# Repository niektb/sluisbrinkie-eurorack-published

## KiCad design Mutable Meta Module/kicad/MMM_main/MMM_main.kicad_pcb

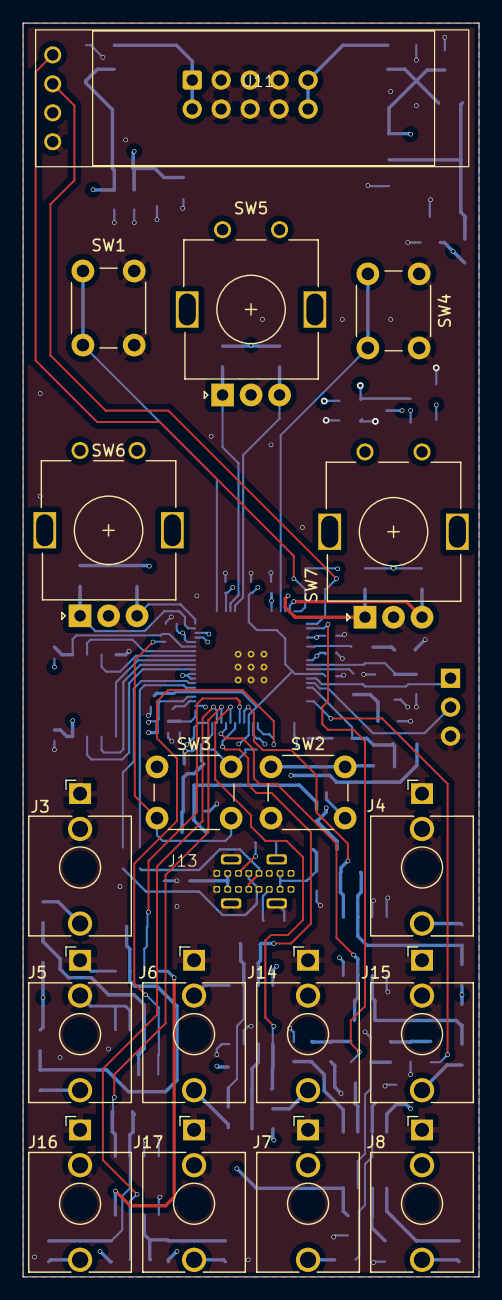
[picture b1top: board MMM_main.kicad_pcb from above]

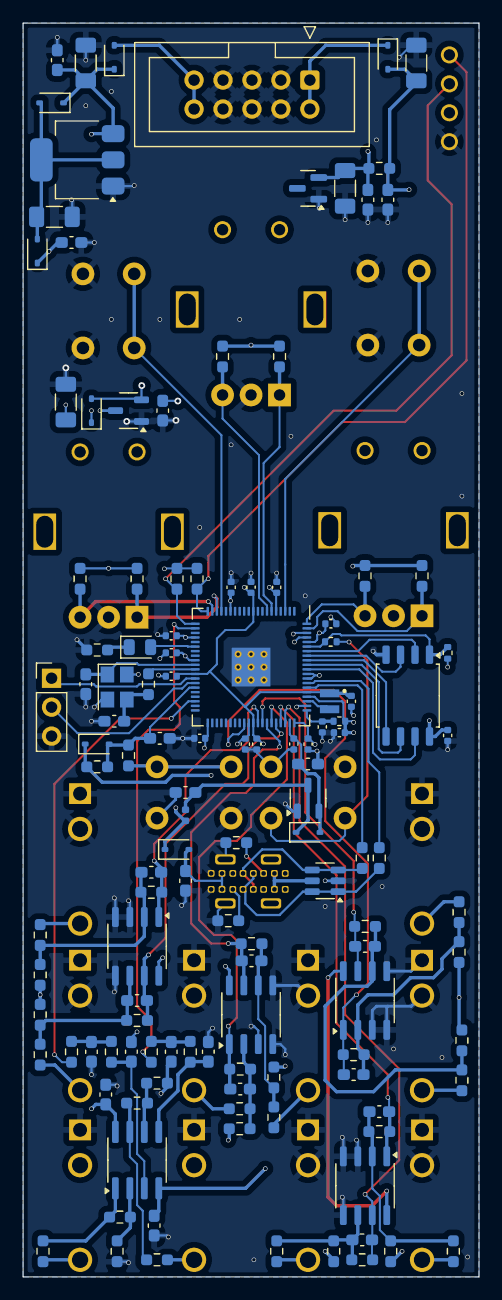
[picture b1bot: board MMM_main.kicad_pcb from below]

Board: 4 copper layers, 40.0 x 110.0 mm, 145 parts (126 on the bottom side), 83 nets.

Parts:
C1, C2, C3, C4, C12: 22uF; C_1206_3216Metric_Pad1.33x1.80mm_HandSolder
C5, C11, C13, C14, C17, C42, C43, C51: 100n; C_0603_1608Metric_Pad1.08x0.95mm_HandSolder
C7, C9, C10, C28: 4.7u; C_0402_1005Metric
C8, C15, C18, C19, C20, C21, C22, C23, C24, C25, C26, C27: 100n; C_0402_1005Metric
C16, C29, C44: 4u7F; C_0603_1608Metric_Pad1.08x0.95mm_HandSolder
C30, C34, C37, C38, C45, C46, C47, C48: 1n; C_0603_1608Metric_Pad1.08x0.95mm_HandSolder
C31, C35: 33p; C_0603_1608Metric_Pad1.08x0.95mm_HandSolder
C32, C41: 10n; C_0603_1608Metric_Pad1.08x0.95mm_HandSolder
C36, C40: 4n7; C_0603_1608Metric_Pad1.08x0.95mm_HandSolder
D6: C2290; LED_0805_2012Metric
D9, D10, D11, D12, D13, D14, D15, D16: 1N5819WS; D_SOD-323
FB1: BLM15H; L_0402_1005Metric
J1: Eurorack Power; IDC-Header_2x05_P2.54mm_Vertical
J2: Conn_01x03; PinHeader_1x03_P2.54mm_Vertical
J3: CV1; Jack_3.5mm_QingPu_WQP-PJ398SM_Vertical_CircularHoles_3D
J4: CV2; Jack_3.5mm_QingPu_WQP-PJ398SM_Vertical_CircularHoles_3D
J5: CV3; Jack_3.5mm_QingPu_WQP-PJ398SM_Vertical_CircularHoles_3D
J6: CV4; Jack_3.5mm_QingPu_WQP-PJ398SM_Vertical_CircularHoles_3D
J7: OUT1; Jack_3.5mm_QingPu_WQP-PJ398SM_Vertical_CircularHoles_3D
J8: OUT2; Jack_3.5mm_QingPu_WQP-PJ398SM_Vertical_CircularHoles_3D
J13: USB_C_Receptacle_USB2.0_16P; UJ20-C-V-C-2-SMT-TR
J14: CV5; Jack_3.5mm_QingPu_WQP-PJ398SM_Vertical_CircularHoles_3D
J15: CV6; Jack_3.5mm_QingPu_WQP-PJ398SM_Vertical_CircularHoles_3D
J16: CV7; Jack_3.5mm_QingPu_WQP-PJ398SM_Vertical_CircularHoles_3D
J17: CV8; Jack_3.5mm_QingPu_WQP-PJ398SM_Vertical_CircularHoles_3D
L1: AOTA-B201610S3R3-101-T; L_pol_2016
R1: 10k; R_0402_1005Metric
R2, R7, R11, R14, R21, R34, R41, R45, R47, R49: 200k; R_0603_1608Metric_Pad0.98x0.95mm_HandSolder
R3: 33; R_0402_1005Metric
R4, R8, R15, R20, R22, R36, R40, R46, R48, R50: 100k; R_0603_1608Metric_Pad0.98x0.95mm_HandSolder
R5, R12, R27, R28, R51, R52, R53, R54: 33k; R_0603_1608Metric_Pad0.98x0.95mm_HandSolder
R6: 1k; R_0402_1005Metric
R13: 2k; R_0603_1608Metric_Pad0.98x0.95mm_HandSolder
R16, R25, R26, R29, R30, R31, R32: 10k; R_0603_1608Metric_Pad0.98x0.95mm_HandSolder
R17: 330R; R_0603_1608Metric_Pad0.98x0.95mm_HandSolder
R18, R19: 27R; R_0603_1608Metric_Pad0.98x0.95mm_HandSolder
R23, R24, R33, R42: 1k; R_0603_1608Metric_Pad0.98x0.95mm_HandSolder
R35, R37, R38, R39: 3k9; R_0603_1608Metric_Pad0.98x0.95mm_HandSolder
R43, R44: 2k2; R_0603_1608Metric_Pad0.98x0.95mm_HandSolder
R55, R56: 5k1; R_0603_1608Metric_Pad0.98x0.95mm_HandSolder
SW1, SW2, SW3, SW4: SW_Push; SW_PUSH_6mm_H13mm
SW5, SW6, SW7: RotaryEncoder; RotaryEncoder_Alps_EC11E_Vertical_H20mm
U1: RP2350_80QFN; RP2350-QFN-80-1EP_10x10_P0.4mm_EP3.4x3.4mm_ThermalVias
U2: AMS1117-5.0; SOT-223-3_TabPin2
U4: W25Q128JVS; SOIC-8_5.3x5.3mm_P1.27mm
U5, U12: XC6206P332MR; SOT-23-3
U6, U9, U13, U14: MCP6002-I-SN; SO-8_3.9x4.9mm_P1.27mm
U7: LM4040DBZ-10; SOT-23
U8: TL072; SOIC-8_3.9x4.9mm_P1.27mm
U10: USBLC6-2SC6; SOT-23-6
U11: SSD1306; OLED_0.91inch
Y1: ABM8-272-T3; Crystal_SMD_3225-4Pin_3.2x2.5mm

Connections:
+1V1: C8.1, C9.1, C10.1, C18.1, L1.1, U1.10 (DVDD), U1.32 (DVDD), U1.51 (DVDD), U1.65 (VREG_FB)
+3V3: C7.1, C15.1, C19.1, C20.1, C21.1, C22.1, C23.1, C24.1, C25.1, C26.1, C29.1, D13.2 (A), D15.1 (K), R1.1, R3.1, R16.2, R25.2, R26.2, R29.2, R30.2, R31.2, R32.2, R43.2, R44.2, U1.5 (IOVDD), U1.15 (IOVDD), U1.24 (IOVDD), U1.29 (IOVDD), U1.41 (IOVDD), U1.50 (IOVDD), U1.60 (IOVDD), U1.64 (VREG_VIN), U1.68 (USB_OTP_VDD), U1.69 (QSPI_IOVDD), U1.76 (IOVDD), U4.8 (VCC), U5.2 (VO), U6.8 (V+), U9.8 (V+), U11.3 (VCC), U13.8 (V+), U14.8 (V+)
+3V3A: C27.1, C44.1, D16.2 (A), U1.59 (ADC_AVDD), U12.2 (VO)
+5V: C3.1, C17.1, D9.1 (K), D13.1 (K), D14.1 (K), FB1.1, U5.3 (VI)
+12V: C1.1, C5.1, C42.1, D10.1 (K), D12.1 (K), U2.3 (VI), U8.8 (V+)
-12V: C2.2, C11.1, C43.2, D11.2 (A), R13.1, U8.4 (V-)
/-10V_REF: C12.1, C13.1, R2.2, R7.2, R11.2, R13.2, R14.2, R21.2, R45.2, R47.2, R49.2, U7.2 (A)
/CC1: J13.A5 (CC1), R55.1
/CC2: J13.B5 (CC2), R56.1
/CV1: C30.2, R5.1, U1.49 (GPIO40_ADC0), U6.1
/CV1_JACK: J3.T, R4.2
/CV2: C34.2, R12.1, U1.52 (GPIO41_ADC1), U9.1
/CV2_JACK: J4.T, R8.2
/CV3: C37.2, R27.1, U1.53 (GPIO42_ADC2), U6.7
/CV3_JACK: J5.T, R15.2
/CV4: C38.2, R28.1, U1.54 (GPIO43_ADC3), U13.7
/CV4_JACK: J6.T, R22.2
/CV5: C45.2, R51.1, U1.55 (GPIO44_ADC4), U13.1
/CV5_JACK: J14.T, R20.2
/CV6: C46.2, R52.1, U1.56 (GPIO45_ADC5), U9.7
/CV6_JACK: J15.T, R46.2
/CV7: C47.2, R53.1, U1.57 (GPIO46_ADC6), U14.1
/CV7_JACK: J16.T, R48.2
/CV8: C48.2, R54.1, U1.58 (GPIO47_ADC7), U14.7
/CV8_JACK: J17.T, R50.2
/D+: J13.A6 (D+), J13.B6 (D+), R18.2, U10.1 (I/O1), U10.6 (I/O1)
/D-: J13.A7 (D-), J13.B7 (D-), R19.1, U10.3 (I/O2), U10.4 (I/O2)
/DM: R19.2, U1.66 (USB_DM)
/DP: R18.1, U1.67 (USB_DP)
/ENC1A: R25.1, SW5.A, U1.6 (GPIO8)
/ENC1B: R26.1, SW5.B, U1.7 (GPIO9)
/ENC2A: R30.1, SW6.A, U1.79 (GPIO2)
/ENC2B: R29.1, SW6.B, U1.80 (GPIO3)
/ENC3A: R32.1, SW7.A, U1.18 (GPIO18)
/ENC3B: R31.1, SW7.B, U1.19 (GPIO19)
/OUT1: R37.2, U1.22 (GPIO22)
/OUT2: R38.2, U1.38 (GPIO30)
/QSPI_SCLK: U1.71 (QSPI_SCLK), U4.6 (CLK)
/QSPI_SD0: U1.72 (QSPI_SD0), U4.5 (DI(IO0))
/QSPI_SD1: U1.74 (QSPI_SD1), U4.2 (DO(IO1))
/QSPI_SD2: U1.73 (QSPI_SD2), U4.3 (IO2)
/QSPI_SD3: U1.70 (QSPI_SD3), U4.7 (IO3)
/QSPI_SS: R1.2, R6.1, U1.75 (QSPI_SS), U4.1 (~CS)
/RESET: R17.1, SW2.2
/SCL: R43.1, U1.21 (GPIO21), U11.2 (SCL)
/SDA: R44.1, U1.20 (GPIO20), U11.1 (SDA)
/SW1: SW1.2, U1.3 (GPIO6)
/SW2: SW4.2, U1.17 (GPIO17)
/VBUS: C16.1, D9.2 (A), J13.A4 (VBUS), J13.A9 (VBUS), J13.B4 (VBUS), J13.B9 (VBUS), U10.5 (VBUS)
/VREG_LX: L1.2, U1.63 (VREG_LX)
/~USB_BOOT: R6.2, SW3.2
GND: C1.2, C2.1, C3.2, C4.2, C5.2, C7.2, C8.2, C9.2, C10.2, C11.2, C12.2, C13.2, C14.2, C15.2, C16.2, C17.2, C18.2, C19.2, C20.2, C21.2, C22.2, C23.2, C24.2, C25.2, C26.2, C27.2, C28.2, C29.2, C31.2, C32.2, C35.2, C36.2, C40.2, C41.2, C42.2, C43.1, C44.2, C51.2, J1.3, J1.4, J1.5, J1.6, J1.7, J1.8, J2.3, J3.S, J3.TN, J4.S, J4.TN, J5.S, J5.TN, J6.S, J6.TN, J7.S, J8.S, J13.A1 (GND), J13.A12 (GND), J13.B1 (GND), J13.B12 (GND), J13.SH1 (SHIELD), J13.SH2 (SHIELD), J13.SH3 (SHIELD), J13.SH4 (SHIELD), J14.S, J14.TN, J15.S, J15.TN, J16.S, J16.TN, J17.S, J17.TN, R24.1, R36.2, R40.2, R55.2, R56.2, SW1.1, SW2.1, SW3.1, SW4.1, SW5.C, SW6.C, SW7.C, U1.62 (VREG_PGND), U1.81 (GND), U2.1 (GND), U4.4 (GND), U5.1 (GND), U6.3 (+), U6.4 (V-), U6.5 (+), U7.1 (K), U9.3 (+), U9.4 (V-), U9.5 (+), U10.2 (GND), U11.4 (GND), U12.1 (GND), U13.3 (+), U13.4 (V-), U13.5 (+), U14.3 (+), U14.4 (V-), U14.5 (+), Y1.2, Y1.4
unnamed: C35.1, R23.2, Y1.3
unnamed: C36.1, R35.2, R37.1
unnamed: C40.1, R38.1, R39.2
unnamed: D6.2 (A), U1.26 (GPIO25)
unnamed: D6.1 (K), R24.2
unnamed: D10.2 (A), J1.9, J1.10
unnamed: D11.1 (K), J1.1, J1.2
unnamed: C4.1, D12.2 (A), D14.2 (A), U2.2 (VO)
unnamed: C14.1, D15.2 (A), R16.1, R17.2, U1.35 (RUN)
unnamed: C51.1, D16.1 (K), FB1.2, U12.3 (VI)
unnamed: J2.1, U1.33 (SWCLK)
unnamed: J2.2, U1.34 (SWD)
unnamed: J7.T, R33.1
unnamed: J8.T, R42.1
unnamed: R33.2, R34.1, U8.7
unnamed: R41.1, R42.2, U8.1
unnamed: C28.1, R3.2, U1.61 (VREG_AVDD)
unnamed: C31.1, U1.30 (XIN), Y1.1
unnamed: R23.1, U1.31 (XOUT)
unnamed: C30.1, R2.1, R4.1, R5.2, U6.2 (-)
unnamed: C37.1, R14.1, R15.1, R27.2, U6.6 (-)
unnamed: C41.1, R39.1, U8.3 (+)
unnamed: R40.1, R41.2, U8.2 (-)
unnamed: C32.1, R35.1, U8.5 (+)
unnamed: R34.2, R36.1, U8.6 (-)
unnamed: C34.1, R7.1, R8.1, R12.2, U9.2 (-)
unnamed: C46.1, R45.1, R46.1, R52.2, U9.6 (-)
unnamed: C45.1, R11.1, R20.1, R51.2, U13.2 (-)
unnamed: C38.1, R21.1, R22.1, R28.2, U13.6 (-)
unnamed: C47.1, R47.1, R48.1, R53.2, U14.2 (-)
unnamed: C48.1, R49.1, R50.1, R54.2, U14.6 (-)

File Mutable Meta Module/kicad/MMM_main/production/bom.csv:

Designator,Footprint,Quantity,Value,LCSC Part #
"C1, C12, C2, C3, C4",1206,5,22uF,
"C10, C28, C7, C9",0402,4,4.7u,
"C11, C13, C14, C17, C42, C43, C5, C51",0603,8,100n,
"C15, C18, C19, C20, C21, C22, C23, C24, C25, C26, C27, C8",0402,12,100n,
"C16, C29, C44",0603,3,4u7F,
"C30, C34, C37, C38, C45, C46, C47, C48",0603,8,1n,
"C31, C35",0603,2,33p,
"C32, C41",0603,2,10n,
"C36, C40",0603,2,4n7,
"D10, D11, D12, D13, D14, D15, D16, D9",D_SOD-323,8,1N5819WS,
D6,0805,1,C2290,
FB1,0402,1,BLM15H,
J1,IDC-Header_2x05_P2.54mm_Vertical,1,Eurorack Power,
J13,UJ20-C-V-C-2-SMT-TR,1,USB_C_Receptacle_USB2.0_16P,
J14,Jack_3.5mm_QingPu_WQP-PJ398SM_Vertical_CircularHoles_3D,1,CV5,
J15,Jack_3.5mm_QingPu_WQP-PJ398SM_Vertical_CircularHoles_3D,1,CV6,
J16,Jack_3.5mm_QingPu_WQP-PJ398SM_Vertical_CircularHoles_3D,1,CV7,
J17,Jack_3.5mm_QingPu_WQP-PJ398SM_Vertical_CircularHoles_3D,1,CV8,
J3,Jack_3.5mm_QingPu_WQP-PJ398SM_Vertical_CircularHoles_3D,1,CV1,
J4,Jack_3.5mm_QingPu_WQP-PJ398SM_Vertical_CircularHoles_3D,1,CV2,
J5,Jack_3.5mm_QingPu_WQP-PJ398SM_Vertical_CircularHoles_3D,1,CV3,
J6,Jack_3.5mm_QingPu_WQP-PJ398SM_Vertical_CircularHoles_3D,1,CV4,
J7,Jack_3.5mm_QingPu_WQP-PJ398SM_Vertical_CircularHoles_3D,1,OUT1,
J8,Jack_3.5mm_QingPu_WQP-PJ398SM_Vertical_CircularHoles_3D,1,OUT2,
L1,L_pol_2016,1,AOTA-B201610S3R3-101-T,
R1,0402,1,10k,
"R11, R14, R2, R21, R34, R41, R45, R47, R49, R7",0603,10,200k,
"R12, R27, R28, R5, R51, R52, R53, R54",0603,8,33k,
R13,0603,1,2k,
"R15, R20, R22, R36, R4, R40, R46, R48, R50, R8",0603,10,100k,
"R16, R25, R26, R29, R30, R31, R32",0603,7,10k,
R17,0603,1,330R,
"R18, R19",0603,2,27R,
"R23, R24, R33, R42",0603,4,1k,
R3,0402,1,33,
"R35, R37, R38, R39",0603,4,3k9,
"R43, R44",0603,2,2k2,
"R55, R56",0603,2,5k1,
R6,0402,1,1k,
"SW1, SW2, SW3, SW4",SW_PUSH_6mm_H13mm,4,SW_Push,
"SW5, SW6, SW7",RotaryEncoder_Alps_EC11E_Vertical_H20mm,3,RotaryEncoder,
U1,RP2350-QFN-80-1EP_10x10_P0.4mm_EP3.4x3.4mm_ThermalVias,1,RP2350_80QFN,
U10,SOT-23-6,1,USBLC6-2SC6,
U11,OLED_0.91inch,1,SSD1306,
"U12, U5",SOT-23-3,2,XC6206P332MR,
"U13, U14, U6, U9",SO-8_3.9x4.9mm_P1.27mm,4,MCP6002-I-SN,
U2,SOT-223-3_TabPin2,1,AMS1117-5.0,
U4,SOIC-8_5.3x5.3mm_P1.27mm,1,W25Q128JVS,
U7,SOT-23,1,LM4040DBZ-10,
U8,SOIC-8_3.9x4.9mm_P1.27mm,1,TL072,
Y1,Crystal_SMD_3225-4Pin_3.2x2.5mm,1,ABM8-272-T3,
